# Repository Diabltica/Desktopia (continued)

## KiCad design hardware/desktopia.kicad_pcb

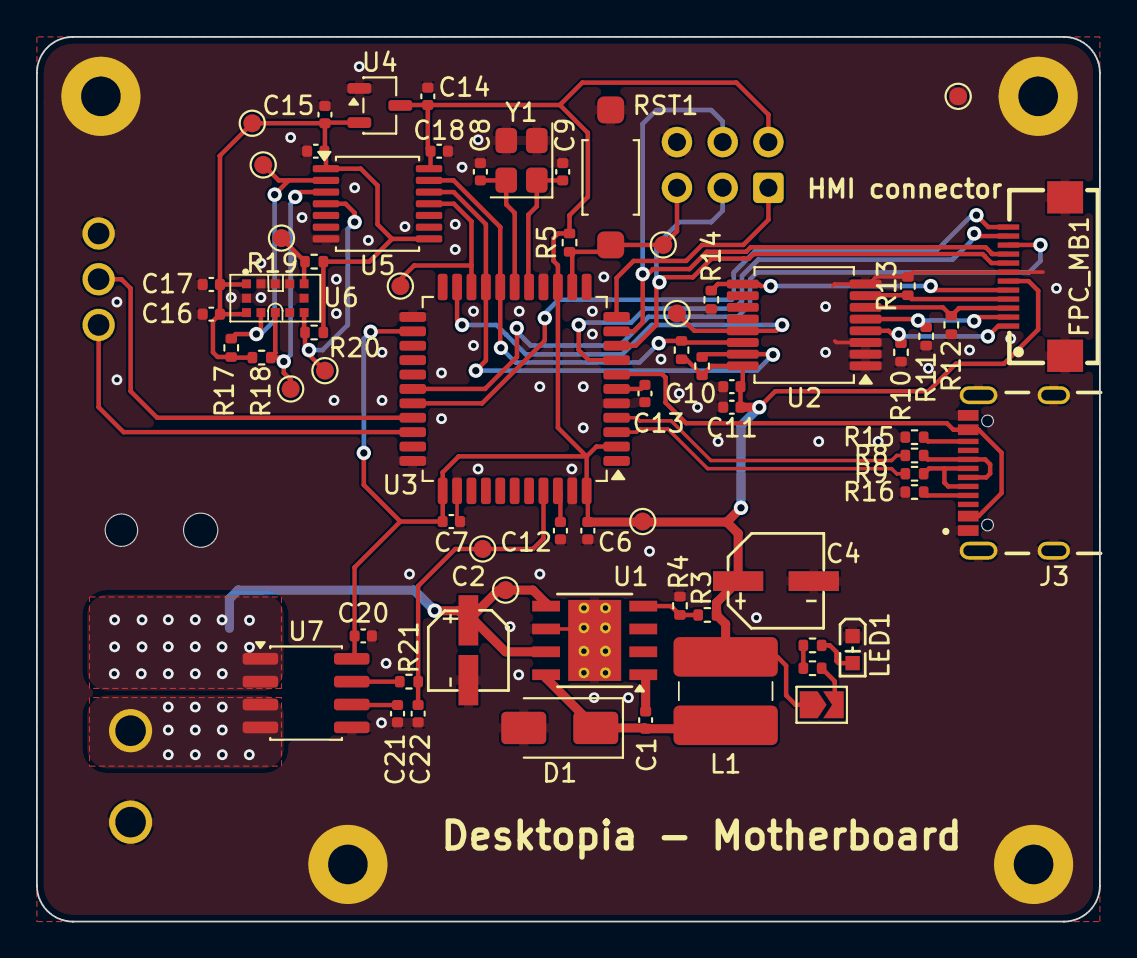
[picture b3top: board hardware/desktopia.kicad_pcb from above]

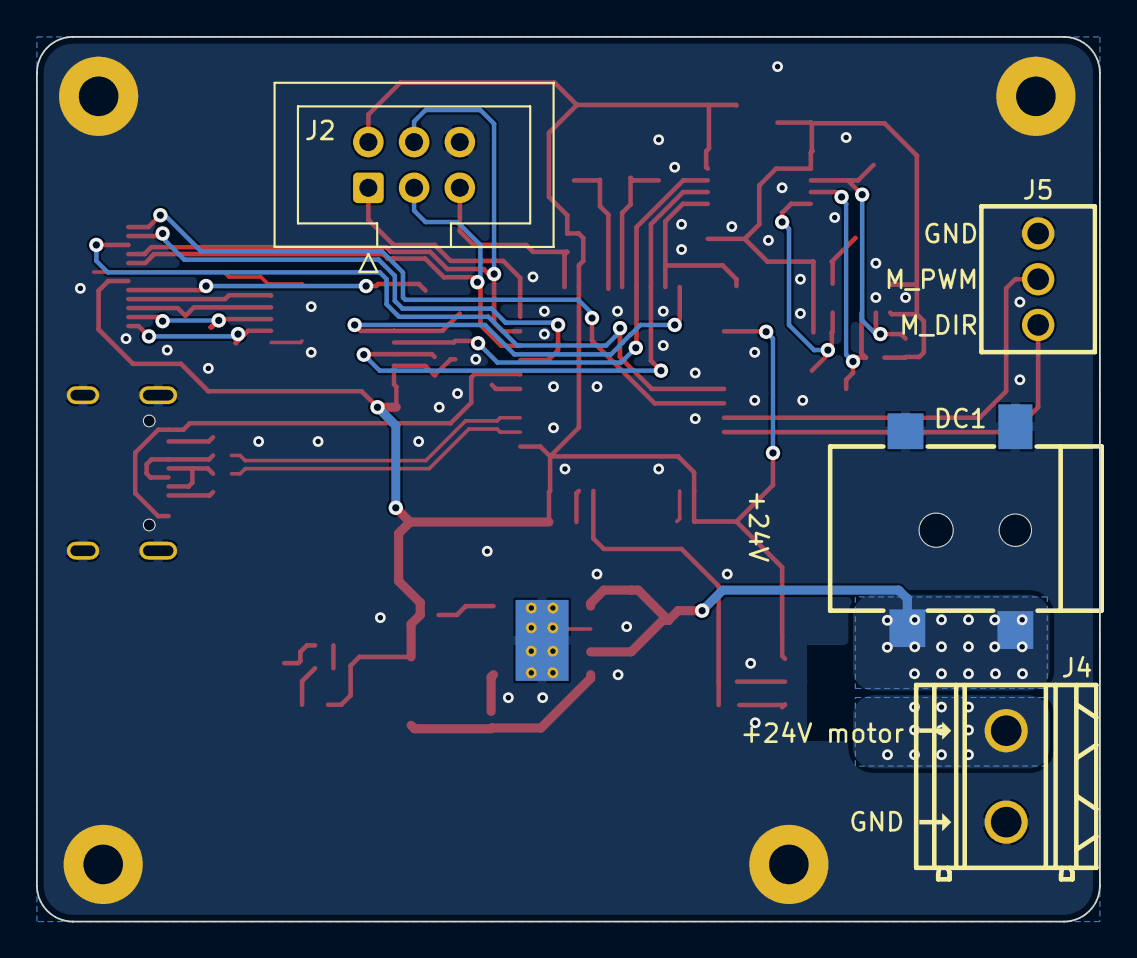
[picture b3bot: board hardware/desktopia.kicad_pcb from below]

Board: 2 copper layers, 59.1 x 49.1 mm, 76 parts (4 on the bottom side), 47 nets.

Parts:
C1: 10nF; C_0402_1005Metric
C2: 4.7uF; RVT1H4R7M0405_C18221489
C4: 33uF; VE-330M1A0505-TRO
C6, C7, C10, C12, C17, C18, C19, C20: 100nF; C_0402_1005Metric
C8, C9: 10pF; C_0402_1005Metric
C11, C13, C14, C15: 1uF; C_0402_1005Metric
C16: 4.7uF; C_0402_1005Metric
C21: 1nF; C_0402_1005Metric
C22: 100pF; C_0402_1005Metric
D1: SS14; D_SMA
DC1: DC050-2_5-T
FPC_MB1: F2D12U-A1G1-ER
H1, H1#2, H1#3, H2: MountingHole_Pad; MountingHole_2.2mm_M2_Pad
J2: Prog_Connector; IDC-Header_2x03_P2.54mm_Vertical
J3: USB4105GFA; GCT_USB4105GFA
J4: PowerMotor; C508128L-2P0G36
J5: MotorCommandCon; ZX-DG28L-2_54-3P
JP1: SolderJumper_2_Open; SolderJumper-2_P1.3mm_Open_TrianglePad1.0x1.5mm
L1: 84uH; L5.8
LED1: KT-0603R
R1, R2, R21: 100; R_0402_1005Metric
R3, R5, R10, R11, R12, R13, R14, R19, R20: 10k; R_0402_1005Metric
R4, R6, R7, R17, R18: 3.3k; R_0402_1005Metric
R8, R9: 22; R_0402_1005Metric
R15, R16: 5.1k; R_0402_1005Metric
RST1: SW_Push; DTS41
TP1, TP7, TP8, TP9, TP10, TP11, TP14, TP15, TP16, TP17, TP18, TP19: TestPoint; TestPoint_Pad_D1.0mm
U1: TPS5430DDA; TI_SO-PowerPAD-8_ThermalVias
U2: TCA9554DB; SSOP-16_5.3x6.2mm_P0.65mm
U3: ATmega32U4-A; TQFP-44_10x10mm_P0.8mm
U4: XC6206P282MR; SOT-23-3
U5: TXS0104EPW; TSSOP-14_4.4x5mm_P0.65mm
U6: VL53L1CBV0FY_1
U7: CC6905S8-5FB005; SOP-8_3.76x4.96mm_P1.27mm
Y1: X322516MLB4SI; Crystal_SMD_3225-4Pin_3.2x2.5mm

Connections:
+2V8: C15.2, C16.1, C17.1, C19.1, R17.1, R18.1, R19.1, R20.1, TP11.1 (1_1), U4.2 (Vout), U5.1 (V_{CCA}), U5.8 (OE), U6.1 (AVDDVCSEL), U6.11 (AVDD)
+5V: C4.1, C6.2, C7.2, C10.2, C11.2, C14.2, C18.1, C20.2, FPC_MB1.6, J2.2, JP1.1 (A), L1.2, R3.1, R5.1, R6.1, R7.1, TP10.1 (1_1), U2.16 (VDD), U3.2 (UVCC), U3.14 (VCC), U3.24 (AVCC), U3.34 (VCC), U3.44 (AVCC), U4.3 (Vin), U5.14 (V_{CCB}), U7.8 (VCC)
+24V: C2.1, DC1.4, TP1.1 (1_1), U1.5 (EN), U1.7 (VIN), U7.1 (IP+), U7.2 (IP+)
/CS_MBside: FPC_MB1.11, U3.8 (PB0)
/D+: R8.2, U3.4 (D+)
/D-: R9.2, U3.3 (D-)
/DC_MBside: FPC_MB1.10, U3.28 (PB4)
/GPIO1_VL53: TP14.1 (1_1), U3.20 (PD2), U5.11 (B3)
/HMI_~INT: TP8.1 (1_1), U2.13 (~INT), U3.21 (PD3)
/Imotor: C22.2, R21.2, TP19.1 (1_1), U3.41 (PF0)
/MISO: J2.1, U3.11 (PB3)
/MOSI: FPC_MB1.9, J2.4, U3.10 (PB2)
/Mdir: J5.1, U3.31 (PC6)
/Mpwm: J5.2, U3.30 (PB6)
/RESET: J2.5, R5.2, RST1.2, TP7.1 (1_1), U3.13 (~RESET)
/RST_MBside: FPC_MB1.12, U3.29 (PB5)
/SCK: FPC_MB1.8, J2.3, U3.9 (PB1)
/SCL: R6.2, U2.14 (SCL), U3.18 (PD0), U5.13 (B1)
/SDA: R7.2, U2.15 (SDA), U3.19 (PD1), U5.12 (B2)
/SW1_MBside: FPC_MB1.1, R10.1, U2.4 (P0)
/SW2_MBside: FPC_MB1.2, R11.1, U2.5 (P1)
/SW3_MBside: FPC_MB1.3, R12.1, U2.6 (P2)
/SW4_MBside: FPC_MB1.4, R13.1, U2.7 (P3)
/SW5_MBside: FPC_MB1.5, R14.1, U2.9 (P4)
GND: C2.2, C4.2, C6.1, C7.1, C8.1, C9.1, C10.1, C11.1, C12.1, C13.1, C14.1, C15.1, C16.2, C17.2, C18.2, C19.2, C20.1, C21.1, C22.1, D1.2 (A), DC1.2, DC1.3, FPC_MB1.7, FPC_MB1.13, FPC_MB1.14, H1.1 (1_1), H1#2.1 (1_1), H1#3.1 (1_1), H2.1 (1_1), J2.6, J3.A1_B12 (GND), J3.B1_A12 (GND), J3.SH1 (SHELL_GND), J3.SH2 (SHELL_GND), J3.SH3 (SHELL_GND), J3.SH4 (SHELL_GND), J4.2, J5.3, LED1.2 (K), R4.2, R10.2, R11.2, R12.2, R13.2, R14.2, R15.2, R16.2, RST1.1, TP9.1 (1_1), U1.6 (GND), U1.9 (GNDPAD), U2.1 (A0), U2.2 (A1), U2.3 (A2), U2.8 (GND), U3.5 (UGND), U3.15 (GND), U3.23 (GND), U3.33 (~HWB/PE2), U3.35 (GND), U3.43 (GND), U4.1 (GND), U5.7 (GND), U6.2 (AVSSVCSEL), U6.3 (GND), U6.4 (GND2), U6.6 (GND3), U6.12 (GND4), U7.5 (GND), Y1.2 (G), Y1.3 (G)
unnamed: C1.1, D1.1 (K), L1.1, U1.8 (PH)
unnamed: J3.A5 (CC1), R16.1
unnamed: J3.B5 (CC2), R15.1
unnamed: J3.A7 (DN1), J3.B7 (DN2), R9.1
unnamed: J3.A6 (DP1), J3.B6 (DP2), R8.1
unnamed: J4.1, U7.3 (IP-), U7.4 (IP-)
unnamed: JP1.2 (B), R1.1
unnamed: LED1.1 (A), R2.2
unnamed: R1.2, R2.1
unnamed: C1.2, U1.1 (BOOT)
unnamed: R3.2, R4.1, U1.4 (VSENSE)
unnamed: C12.2, U3.42 (AREF)
unnamed: C13.2, U3.6 (UCAP)
unnamed: C8.2, U3.17 (XTAL1), Y1.4
unnamed: C9.2, U3.16 (XTAL2), Y1.1
unnamed: R17.2, TP15.1 (1_1), U5.2 (A1), U6.10 (SCL)
unnamed: R18.2, TP16.1 (1_1), U5.3 (A2), U6.9 (SDA)
unnamed: R20.2, TP17.1 (1_1), U5.4 (A3), U6.7 (GPIO1)
unnamed: R19.2, TP18.1 (1_1), U6.5 (XSHUT)
unnamed: R21.1, U7.7 (VOUT)
unnamed: C21.2, U7.6 (VREF)
VBUS: J3.A4_B9 (VBUS), J3.B4_A9 (VBUS), U3.7 (VBUS)

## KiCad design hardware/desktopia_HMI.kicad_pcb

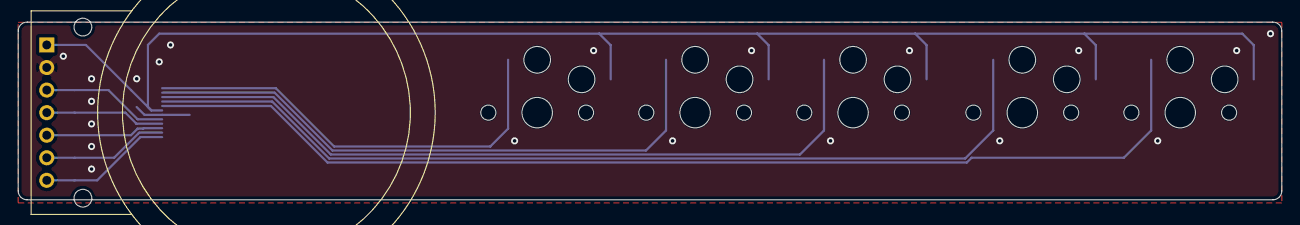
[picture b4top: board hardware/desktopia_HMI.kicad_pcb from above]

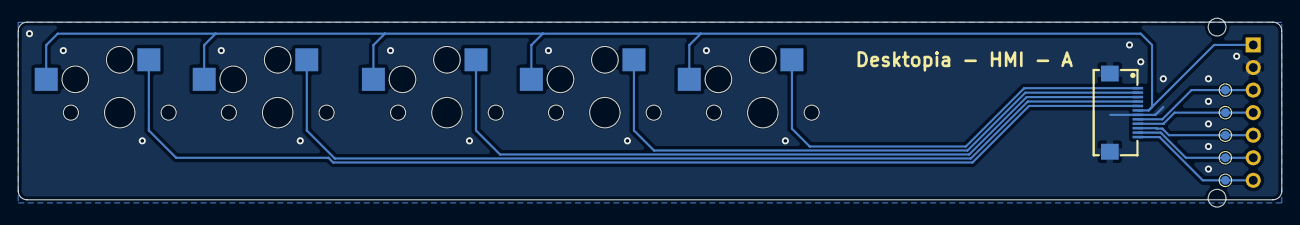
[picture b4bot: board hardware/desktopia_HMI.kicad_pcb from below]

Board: 2 copper layers, 142.2 x 21.3 mm, 12 parts (6 on the bottom side), 12 nets.

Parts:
FPC_HMI1: F2D12U-A1G1-ER
J1: LCD_Connector; LCD_round_screen
SW1, SW2, SW3, SW4, SW5: SW_Push; PG1350
TP2, TP3, TP4, TP5, TP6: TestPoint; TestPoint_Pad_D1.0mm

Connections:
+5VA: FPC_HMI1.6, J1.1, SW1.2, SW2.2, SW3.2, SW4.2, SW5.2
/CS_HMIside: FPC_HMI1.11, J1.6, TP5.1 (1_1)
/DC_HMIside: FPC_HMI1.10, J1.5, TP4.1 (1_1)
/MOSI_HMIside: FPC_HMI1.9, J1.4, TP3.1 (1_1)
/RST_HMIside: FPC_HMI1.12, J1.7, TP6.1 (1_1)
/SCK_HMIside: FPC_HMI1.8, J1.3, TP2.1 (1_1)
/SW1_HMIside: FPC_HMI1.1, SW1.1
/SW2_HMIside: FPC_HMI1.2, SW2.1
/SW3_HMIside: FPC_HMI1.3, SW3.1
/SW4_HMIside: FPC_HMI1.4, SW4.1
/SW5_HMIside: FPC_HMI1.5, SW5.1
GNDA: FPC_HMI1.7, FPC_HMI1.13, FPC_HMI1.14, J1.2

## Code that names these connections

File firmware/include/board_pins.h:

#pragma once
/*
 * Desktopia motherboard – pin map extracted from desktopia.kicad_sch (RJ11 / RS-485 HMI version)
 * ---------------------------------------------------------------------------
 * MCU: ATmega32U4 (TQFP-44), 16 MHz crystal, +5 V.
 * Numbers below are Arduino pin numbers of the PlatformIO "leonardo" variant.
 * (port / TQFP pin / schematic net in the comments)
 */
#include <Arduino.h>

namespace pins {

// --- Motor command, connector J6 "MotorCommandCon" (1 = Mdir, 2 = Mpwm, 3 = GND), 10k pull-downs
constexpr uint8_t MOTOR_DIR = 5;    // PC6  – TQFP 31 – net Mdir
constexpr uint8_t MOTOR_PWM = 10;   // PB6  – TQFP 30 – net Mpwm – OC1B (Timer1 hardware PWM)

// --- Motor driver supply: HIGH = Q5 (P-MOSFET high-side switch) feeds J5. Pull-down R22: off during a reset.
constexpr uint8_t MOTOR_POWER = 6;  // PD7  – TQFP 27 – net MOTOR_PWR
constexpr uint8_t MOTOR_POWER_PORT_BIT = 7;   // PORTD bit, for the register-only cut in interrupts

// --- INA226 alert: open drain, active low, 4.7k pull-up R25, 100 pF filter C23
constexpr uint8_t I_ALERT = 7;      // PE6  – TQFP 1  – net I_ALERT – INT6

// --- HMI board link: RS-485 transceiver U5 (SP485EEN), RJ11 jack J4
//   RX = PD2 (D0) – TQFP 20 – U5 RO            TX = PD3 (D1) – TQFP 21 – U5 DI          → Serial1
constexpr uint8_t RS485_DE = 4;     // PD4  – TQFP 25 – U5 DE and /RE, tied: HIGH = drive the bus

// --- I2C bus: VL53L1CB ToF (0x29) behind the BSS138 level shifters Q1 / Q2 (2.8 V side),
//     INA226 motor current monitor U6 (0x40) on the 5 V side
//   SDA = PD1 (D2), SCL = PD0 (D3): hardware TWI via Wire

// --- Not used by this firmware
//   PB4 (D8) = TOF_INT: VL53L1CB GPIO1 (data ready) through level shifter Q3, 10k pull-up R10 (PCINT4)
//   PF0 (A5) is now free (it read the old analog current sensor)
//   PB1 / PB2 / PB3 (SCK / MOSI / MISO) only go to the ISP header J2

}  // namespace pins

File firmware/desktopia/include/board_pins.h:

#pragma once
/*
 * Desktopia motherboard – pin map extracted from desktopia.kicad_sch (RJ11 / RS-485 HMI version)
 * ---------------------------------------------------------------------------
 * MCU: RP2040 (U4, QFN-56), 12 MHz crystal, 3.3 V I/O (U9). Numbers below are GPIO numbers (GPn).
 * (QFN pin / schematic net in the comments). No pin is 5 V tolerant: every input on this board is at 3.3 V.
 */
#include <Arduino.h>

// The PC simulation (firmware/sim) runs both boards on one pin array: it moves this board's pins out of the way.
#ifndef BOARD_PIN_OFFSET
#define BOARD_PIN_OFFSET 0
#endif

namespace pins {

// --- Motor command: on-board H-bridge (through JP2-JP5) and connector J6 (1 = Mdir, 2 = Mpwm, 3 = GND),
//     10k pull-downs R24 / R26
constexpr uint8_t MOTOR_PWM = 8 + BOARD_PIN_OFFSET;     // GP8  – pin 11 – net Mpwm – PWM slice 4, channel A
constexpr uint8_t MOTOR_DIR = 9 + BOARD_PIN_OFFSET;     // GP9  – pin 12 – net Mdir

// --- Motor driver supply: HIGH = Q5 (P-MOSFET high-side switch) feeds J5 and the bridge. Pull-down R22.
constexpr uint8_t MOTOR_POWER = 12 + BOARD_PIN_OFFSET;  // GP12 – pin 15 – net MOTOR_PWR

// --- DRV8701E (U7), not driven by this firmware yet: nSLEEP stays low (its pull-down), the bridge sleeps
constexpr uint8_t BRIDGE_NSLEEP = 10 + BOARD_PIN_OFFSET;   // GP10 – pin 13 – net nSLEEP
constexpr uint8_t BRIDGE_NFAULT = 11 + BOARD_PIN_OFFSET;   // GP11 – pin 14 – net nFAULT (open drain)

// --- INA226 alert: open drain, active low, 4.7k pull-up R25 to +3V3, 100 pF filter C23
constexpr uint8_t I_ALERT = 7 + BOARD_PIN_OFFSET;       // GP7  – pin 9  – net I_ALERT

// --- HMI board link: RS-485 transceiver U5 (SP3485EN, 3.3 V), RJ11 jack J4. UART0 → Serial1
constexpr uint8_t RS485_RX = 17 + BOARD_PIN_OFFSET;     // GP17 – pin 28 – U5 RO (UART0 RX)
constexpr uint8_t RS485_DE = 18 + BOARD_PIN_OFFSET;     // GP18 – pin 29 – U5 DE and /RE, tied: HIGH = drive the bus
constexpr uint8_t RS485_TX = 28 + BOARD_PIN_OFFSET;     // GP28 – pin 40 – U5 DI (UART0 TX)

// --- I2C bus: INA226 U6 (0x40) on the 3.3 V side (R1 / R5 pull-ups), VL53L1CB U3 (0x29) on the 2.8 V side of the
//     BSS138 level shifters Q1 / Q2
constexpr uint8_t I2C_SDA = 4 + BOARD_PIN_OFFSET;       // GP4  – pin 6  – net SDA (I2C0)
constexpr uint8_t I2C_SCL = 5 + BOARD_PIN_OFFSET;       // GP5  – pin 7  – net SCL (I2C0)

// --- Not used by this firmware
//   GP6 (pin 8) = TOF_INT: VL53L1CB GPIO1 (data ready) through the level shifter Q3, R10 10k pull-up to +3V3
//   GP0-GP3, GP13-GP16, GP19-GP27, GP29: not connected
//   SWD: TP4 SWCLK, TP7 SWDIO. BOOT1 pulls QSPI_SS low (USB bootloader), RST1 pulls RUN low.

}  // namespace pins

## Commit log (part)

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2023-09-25 add readme and some documentation
2023-09-25 change readme extension
2023-09-25 update architecture
2023-09-25 create kicad project
